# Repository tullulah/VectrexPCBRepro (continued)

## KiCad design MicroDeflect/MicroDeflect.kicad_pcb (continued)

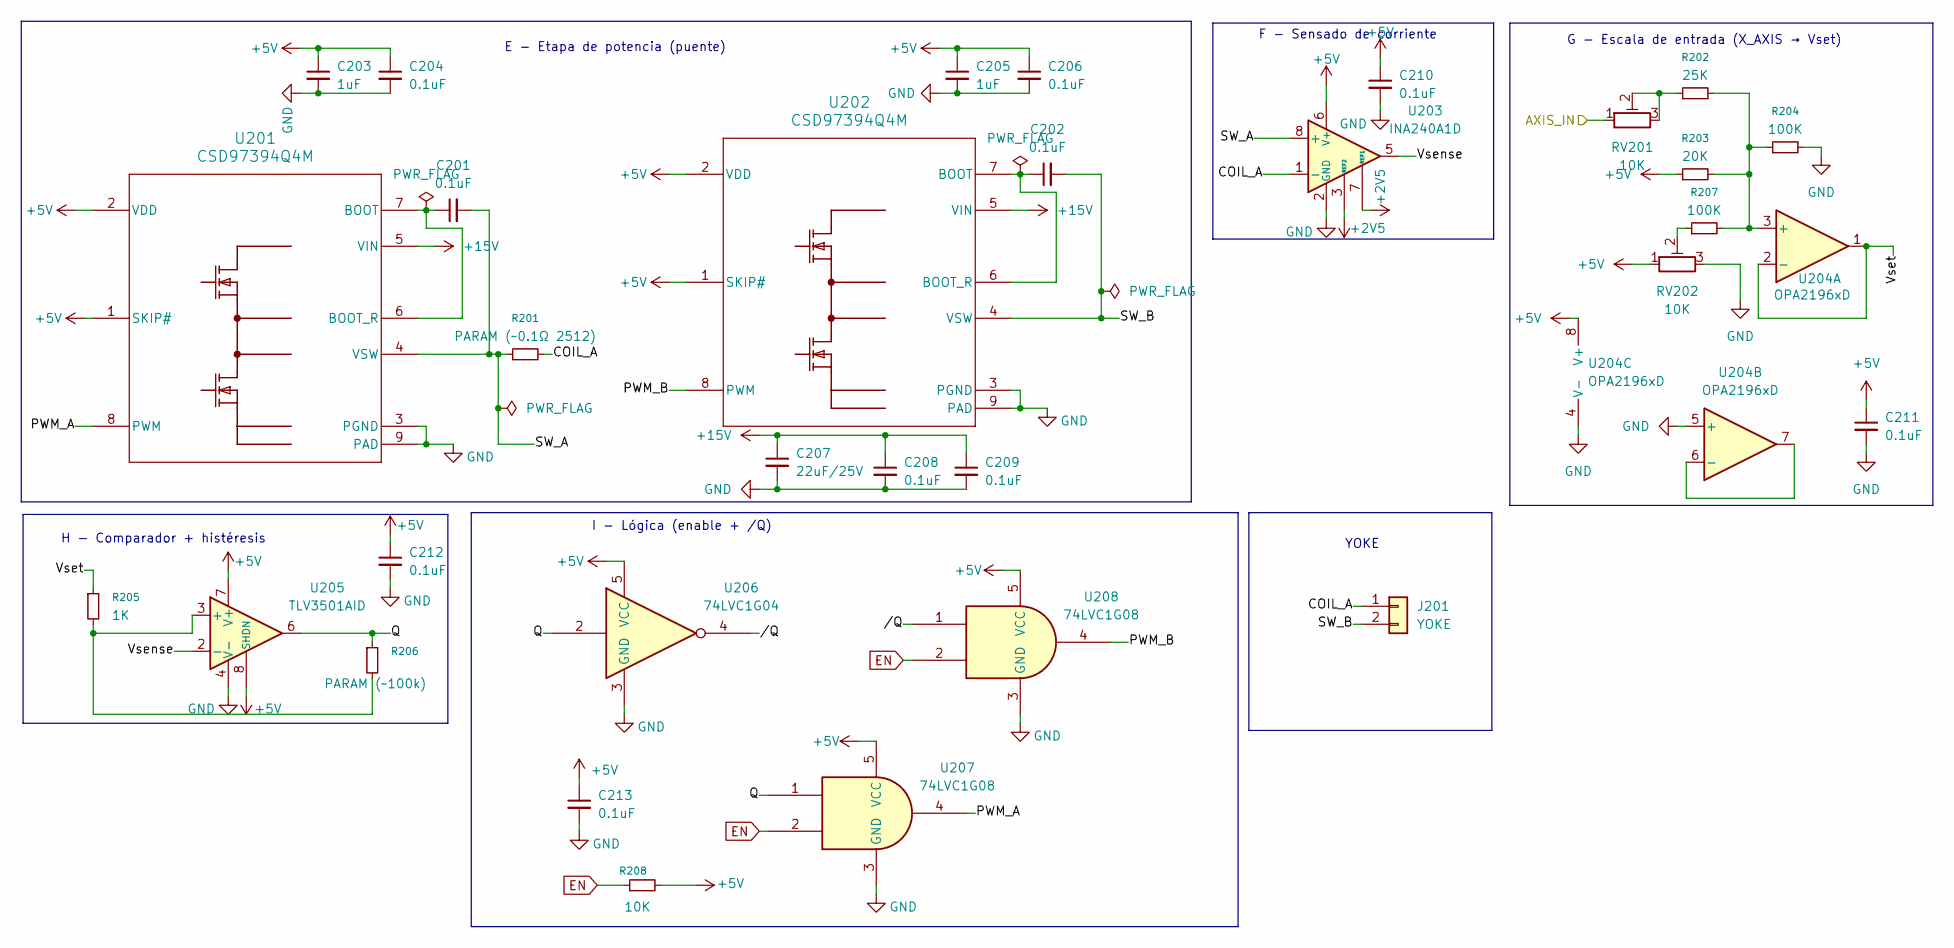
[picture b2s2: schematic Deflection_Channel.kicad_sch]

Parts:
C201, C202, C204, C206, C208, C209, C210, C211, C212, C213: 0.1uF; C_0402_1005Metric
C203, C205: 1uF; C_0402_1005Metric
C207: 22uF/25V; C_1206_3216Metric
J201: YOKE; JST_XH_B2B-XH-AM_1x02_P2.50mm_Vertical
R201: PARAM (~0.1Ω 2512); R_2512_6332Metric
R202: 25K; R_0402_1005Metric
R203: 20K; R_0402_1005Metric
R204, R207: 100K; R_0402_1005Metric
R205: 1K; R_0402_1005Metric
R206: PARAM (~100k); R_0402_1005Metric
R208: 10K; R_0402_1005Metric
RV201, RV202: 10K; Potentiometer_Bourns_3339H_Vertical
U201, U202: CSD97394Q4M; DPC0008A
U203: INA240A1D; SOIC-8_3.9x4.9mm_P1.27mm
U204: OPA2196xD; SOIC-8_3.9x4.9mm_P1.27mm
U205: TLV3501AID; SOIC-8_3.9x4.9mm_P1.27mm
U206: 74LVC1G04; SOT-23-5
U207, U208: 74LVC1G08; SOT-23-5

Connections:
+2V5: U203.3 (REF2), U203.7 (REF1); also elsewhere on the board
+5V: C203.1, C204.1, C205.1, C206.1, C210.1, C211.1, C212.1, C213.1, R203.1, R208.2, RV202.1, U201.1 (SKIP#), U201.2 (VDD), U202.1 (SKIP#), U202.2 (VDD), U203.6 (V+), U204.8 (V+), U205.7 (V+), U205.8 (SHDN), U206.5 (VCC), U207.5 (VCC), U208.5 (VCC); also elsewhere on the board
+15V: C207.1, C208.1, C209.1, U201.5 (VIN), U202.5 (VIN); also elsewhere on the board
/Deflection_Channel_X/AXIS_IN: RV201.1; also elsewhere on the board
/Deflection_Channel_X/COIL_A: J201.1, R201.2, U203.1 (-)
/Deflection_Channel_X/PWM_A: U201.8 (PWM), U207.4
/Deflection_Channel_X/PWM_B: U202.8 (PWM), U208.4
/Deflection_Channel_X/Q: R206.1, U205.6, U206.2, U207.1
/Deflection_Channel_X/SW_A: C201.2, R201.1, U201.4 (VSW), U203.8 (+)
/Deflection_Channel_X/SW_B: C202.2, J201.2, U202.4 (VSW)
/Deflection_Channel_X/Vsense: U203.5, U205.2 (-)
/Deflection_Channel_X/Vset: R205.1, U204.1, U204.2 (-)
/Deflection_Channel_X//Q: U206.4, U208.1
EN: R208.1, U207.2, U208.2; also elsewhere on the board
GND: C203.2, C204.2, C205.2, C206.2, C207.2, C208.2, C209.2, C210.2, C211.2, C212.2, C213.2, R204.2, RV202.3, U201.3 (PGND), U201.9 (PAD), U202.3 (PGND), U202.9 (PAD), U203.2 (GND), U203.4 (GND), U204.4 (V-), U204.5 (+), U205.4 (V-), U206.3 (GND), U207.3 (GND), U208.3 (GND); also elsewhere on the board
unnamed: R202.1, RV201.2, RV201.3
unnamed: R207.1, RV202.2
unnamed: C201.1, U201.6 (BOOT_R), U201.7 (BOOT)
unnamed: C202.1, U202.6 (BOOT_R), U202.7 (BOOT)
unnamed: R202.2, R203.2, R204.1, R207.2, U204.3 (+)
unnamed: U204.6 (-), U204.7
unnamed: R205.2, R206.2, U205.3 (+)

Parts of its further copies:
C301, C302, C304, C306, C308, C309, C310, C311, C312, C313: 0.1uF; C_0402_1005Metric
C303, C305: 1uF; C_0402_1005Metric
C307: 22uF/25V; C_1206_3216Metric
J301: YOKE; JST_XH_B2B-XH-AM_1x02_P2.50mm_Vertical
R301: PARAM (~0.1Ω 2512); R_2512_6332Metric
R302: 25K; R_0402_1005Metric
R303: 20K; R_0402_1005Metric
R304, R307: 100K; R_0402_1005Metric
R305: 1K; R_0402_1005Metric
R306: PARAM (~100k); R_0402_1005Metric
R308: 10K; R_0402_1005Metric
RV301, RV302: 10K; Potentiometer_Bourns_3339H_Vertical
U301, U302: CSD97394Q4M; DPC0008A
U303: INA240A1D; SOIC-8_3.9x4.9mm_P1.27mm
U304: OPA2196xD; SOIC-8_3.9x4.9mm_P1.27mm
U305: TLV3501AID; SOIC-8_3.9x4.9mm_P1.27mm
U306: 74LVC1G04; SOT-23-5
U307, U308: 74LVC1G08; SOT-23-5

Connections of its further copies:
+2V5: U303.3 (REF2), U303.7 (REF1); also elsewhere on the board
+5V: C303.1, C304.1, C305.1, C306.1, C310.1, C311.1, C312.1, C313.1, R303.1, R308.2, RV302.1, U301.1 (SKIP#), U301.2 (VDD), U302.1 (SKIP#), U302.2 (VDD), U303.6 (V+), U304.8 (V+), U305.7 (V+), U305.8 (SHDN), U306.5 (VCC), U307.5 (VCC), U308.5 (VCC); also elsewhere on the board
+15V: C307.1, C308.1, C309.1, U301.5 (VIN), U302.5 (VIN); also elsewhere on the board
/Deflection_Channel_Y/AXIS_IN: RV301.1; also elsewhere on the board
/Deflection_Channel_Y/COIL_A: J301.1, R301.2, U303.1 (-)
/Deflection_Channel_Y/PWM_A: U301.8 (PWM), U307.4
/Deflection_Channel_Y/PWM_B: U302.8 (PWM), U308.4
/Deflection_Channel_Y/Q: R306.1, U305.6, U306.2, U307.1
/Deflection_Channel_Y/SW_A: C301.2, R301.1, U301.4 (VSW), U303.8 (+)
/Deflection_Channel_Y/SW_B: C302.2, J301.2, U302.4 (VSW)
/Deflection_Channel_Y/Vsense: U303.5, U305.2 (-)
/Deflection_Channel_Y/Vset: R305.1, U304.1, U304.2 (-)
/Deflection_Channel_Y//Q: U306.4, U308.1
EN: R308.1, U307.2, U308.2; also elsewhere on the board
GND: C303.2, C304.2, C305.2, C306.2, C307.2, C308.2, C309.2, C310.2, C311.2, C312.2, C313.2, R304.2, RV302.3, U301.3 (PGND), U301.9 (PAD), U302.3 (PGND), U302.9 (PAD), U303.2 (GND), U303.4 (GND), U304.4 (V-), U304.5 (+), U305.4 (V-), U306.3 (GND), U307.3 (GND), U308.3 (GND); also elsewhere on the board
unnamed: R302.1, RV301.2, RV301.3
unnamed: R307.1, RV302.2
unnamed: C301.1, U301.6 (BOOT_R), U301.7 (BOOT)
unnamed: C302.1, U302.6 (BOOT_R), U302.7 (BOOT)
unnamed: R302.2, R303.2, R304.1, R307.2, U304.3 (+)
unnamed: U304.6 (-), U304.7
unnamed: R305.2, R306.2, U305.3 (+)

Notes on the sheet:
YOKE
I - Lógica (enable + /Q)
H - Comparador + histéresis
G - Escala de entrada (X_AXIS → Vset)
F - Sensado de corriente
E - Etapa de potencia (puente)

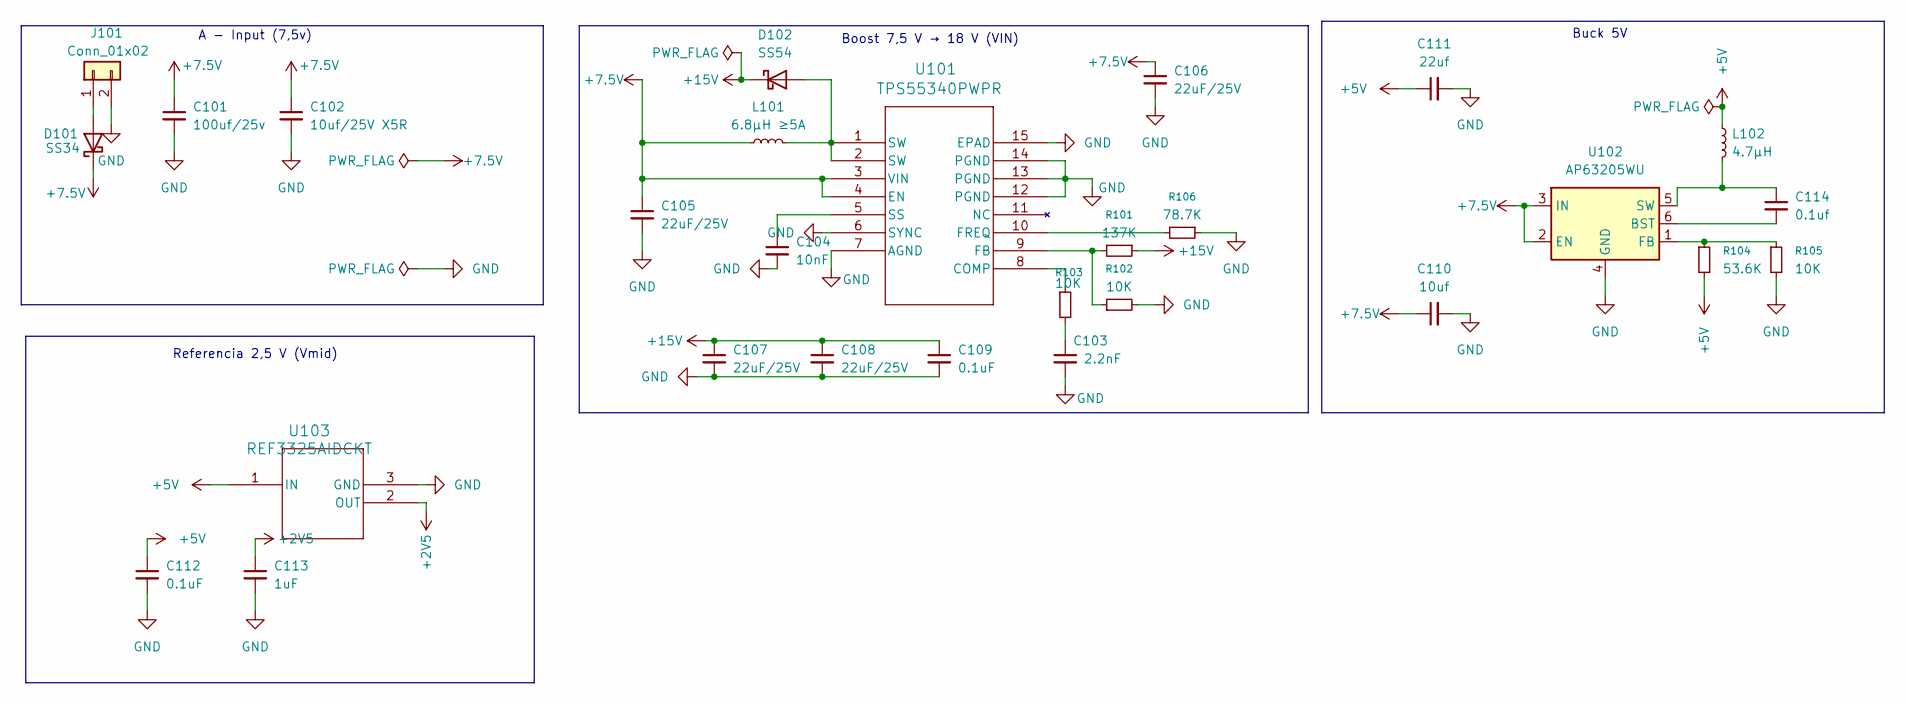
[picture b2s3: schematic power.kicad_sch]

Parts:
C101: 100uf/25v; CP_Elec_6.3x7.7
C102: 10uf/25V X5R; C_0805_2012Metric
C103: 2.2nF; C_0402_1005Metric
C104: 10nF; C_0402_1005Metric
C105, C106, C107, C108: 22uF/25V; C_1206_3216Metric
C109, C112: 0.1uF; C_0402_1005Metric
C110: 10uf; C_0805_2012Metric
C111: 22uf; C_0805_2012Metric
C113: 1uF; C_0402_1005Metric
C114: 0.1uf; C_0402_1005Metric
D101: SS34; D_SMA
D102: SS54; D_SMB
J101: Conn_01x02; JST_VH_B2P-VH-B_1x02_P3.96mm_Vertical
L101: 6.8µH ≥5A; L_12x12mm_H6mm
L102: 4.7µH; L_Bourns_SRN6045TA
R101: 137K; R_0402_1005Metric
R102, R103, R105: 10K; R_0402_1005Metric
R104: 53.6K; R_0402_1005Metric
R106: 78.7K; R_0402_1005Metric
U101: TPS55340PWPR; PWP14
U102: AP63205WU; TSOT-23-6
U103: REF3325AIDCKT; DCK3

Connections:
+2V5: C113.1, U103.2 (OUT); also elsewhere on the board
+5V: C111.1, C112.1, L102.1, R104.2, U103.1 (IN); also elsewhere on the board
+7.5V: C101.1, C102.1, C105.1, C106.1, C110.1, D101.1 (K), L101.1, U101.3 (VIN), U101.4 (EN), U102.2 (EN), U102.3 (IN)
+15V: C107.1, C108.1, C109.1, D102.1 (K), R101.1; also elsewhere on the board
GND: C101.2, C102.2, C103.2, C104.2, C105.2, C106.2, C107.2, C108.2, C109.2, C110.2, C111.2, C112.2, C113.2, J101.2, R102.2, R105.2, R106.1, U101.6 (SYNC), U101.7 (AGND), U101.12 (PGND), U101.13 (PGND), U101.14 (PGND), U101.15 (EPAD), U102.4 (GND), U103.3 (GND); also elsewhere on the board
unnamed: C103.1, R103.2
unnamed: D101.2 (A), J101.1
unnamed: D102.2 (A), L101.2, U101.1 (SW), U101.2 (SW)
unnamed: R103.1, U101.8 (COMP)
unnamed: R101.2, R102.1, U101.9 (FB)
unnamed: R106.2, U101.10 (FREQ)
unnamed: C104.1, U101.5 (SS)
unnamed: C114.2, U102.6 (BST)
unnamed: R104.1, R105.1, U102.1 (FB)
unnamed: C114.1, L102.2, U102.5 (SW)

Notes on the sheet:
Boost 7,5 V → 18 V (VIN)
Referencia 2,5 V (Vmid)
Buck 5V
A - Input (7,5v)

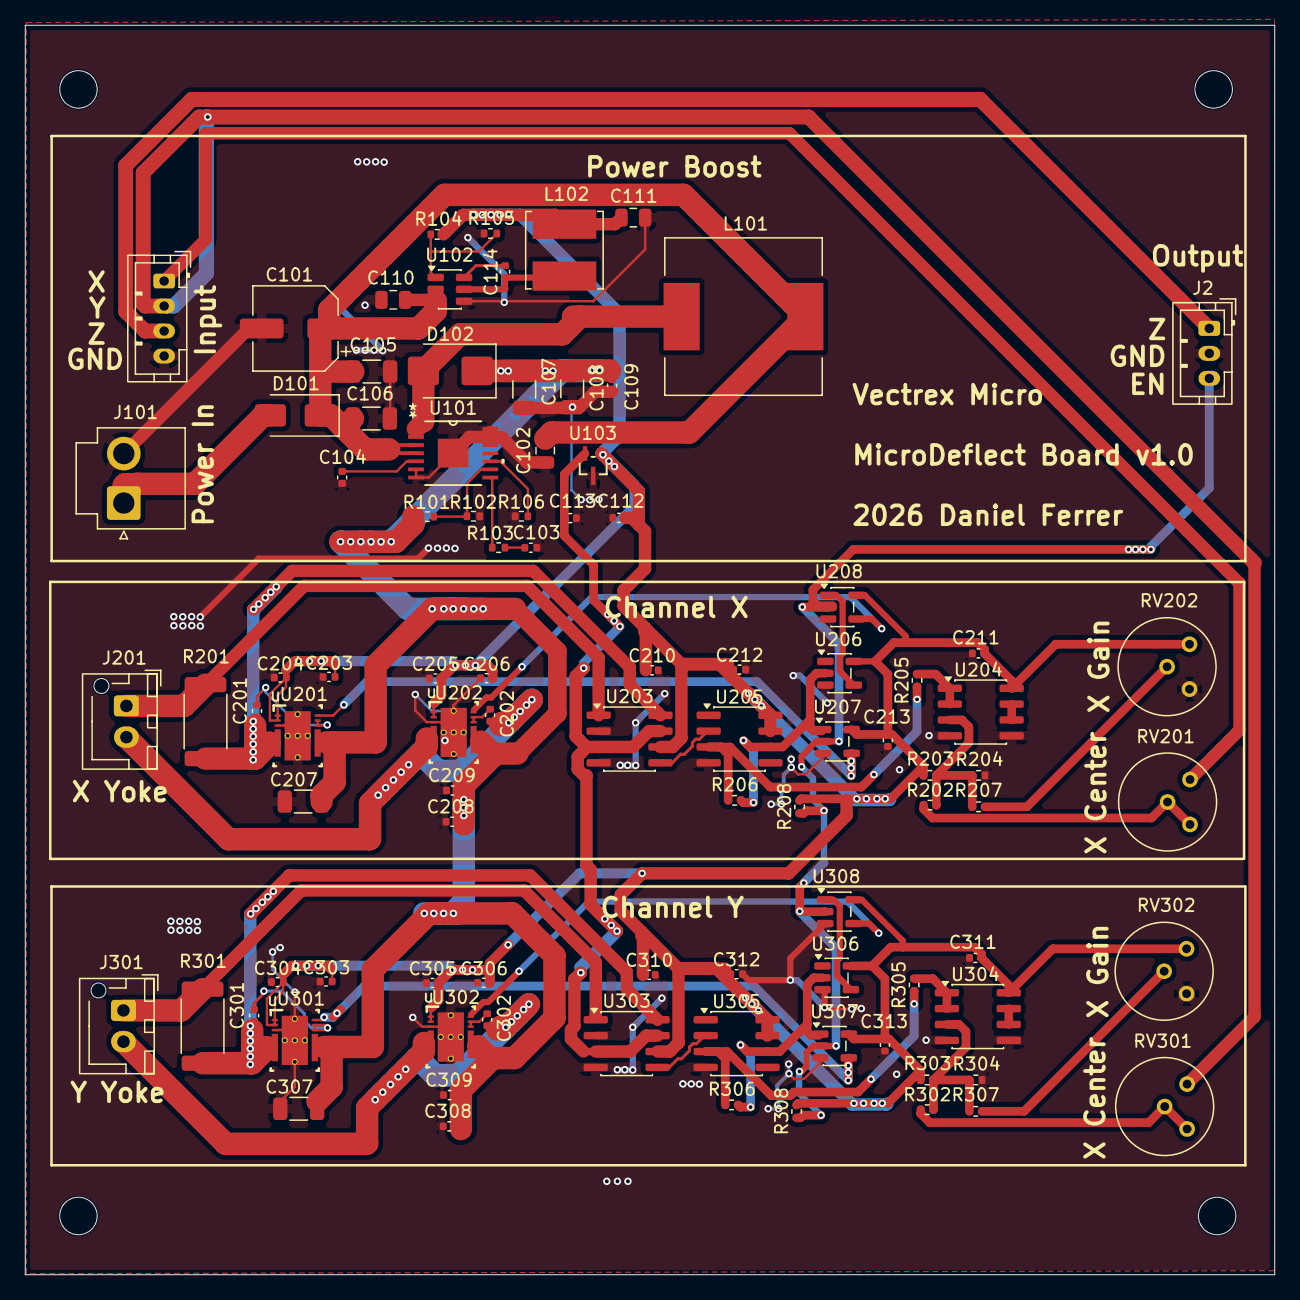
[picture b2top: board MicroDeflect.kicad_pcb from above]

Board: 2 copper layers, 100.0 x 100.0 mm, 98 parts (0 on the bottom side), 51 nets.

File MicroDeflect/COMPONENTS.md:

# Deflection Board — Components by group

Reference-designator scheme: **Power = 1xx · Channel X = 2xx · Channel Y = 3xx**.
`BOM_preliminary.csv` is the flat single-source-of-truth; this file is the readable
grouped view and shows **which sheet each group lives on**.

---

## Sheet: POWER (1xx)

### A — Input 7.5 V
| Ref | Value | Function |
|---|---|---|
| J101 | 7.5V_IN | power input connector |
| D101 | SS34 | reverse-polarity protection |
| C101 | 100µF/25V | input bulk |
| C102 | 10µF/25V | input decoupling |

### B — Boost 7.5 V → 18 V (VIN)
| Ref | Value | Function |
|---|---|---|
| U101 | TPS55340 | boost IC |
| L101 | 6.8µH ≥5A | boost inductor |
| D102 | SS54 | boost rectifier |
| R101 | 137k | FB top (→18V) |
| R102 | 10k | FB bottom |
| R103 | 10k | COMP R (per datasheet) |
| C103 | 2.2nF | COMP C (per datasheet) |
| C104 | 10nF | soft-start (per datasheet) |
| C105, C106 | 22µF/25V | boost input |
| C107, C108 | 22µF/25V | boost output |
| C109 | 0.1µF | boost output HF |

### C — Buck 5 V
| Ref | Value | Function |
|---|---|---|
| U102 | AP63205 | buck IC (from +7V5) |
| L102 | 4.7µH | buck inductor |
| R104 | 53.6k | FB top (→5V) |
| R105 | 10k | FB bottom |
| C110 | 10µF | buck input |
| C111 | 22µF | buck output |

### D — 2.5 V reference (Vmid)
| Ref | Value | Function |
|---|---|---|
| U103 | REF3325 | 2.5V reference |
| C112 | 0.1µF | decoupling |
| C113 | 1µF | decoupling |

---

## Sheet: DEFLECTION_CHANNEL — X = 2xx · Y = 3xx (same parts)

### E — Power stage (H-bridge)
| Ref | Value | Function |
|---|---|---|
| U201 | CSD97394Q4M | leg A |
| U202 | CSD97394Q4M | leg B |
| R201 | **PARAMETRIC** (~0.1Ω 2512) | R_sense (shunt) |
| C201, C202 | 0.1µF | BOOT leg A / B |
| C203, C205 | 1µF | VDD leg A / B |
| C204, C206 | 0.1µF | VDD HF leg A / B |
| C207 | 22µF/25V | VIN local bulk |
| C208, C209 | 0.1µF | VIN local A / B |

### F — Current sense
| Ref | Value | Function |
|---|---|---|
| U203 | INA240A1 | current sense (REF=Vmid) |
| C210 | 0.1µF | decoupling |

### G — Input scale (X_AXIS → Vset)
| Ref | Value | Function |
|---|---|---|
| U204 | OPA2196 | buffer (unit A; unit B spare) |
| C211 | 0.1µF | decoupling |
| R202 | 25k | Rin1 (from X_AXIS) |
| R203 | 20k | Rin2 (from +5V, offset) |
| R204 | 100k | Rf (to GND) |
| RV201 | 10k | gain trim (optional) |
| RV202 | 10k | offset/centering trim (optional) |

### H — Comparator + hysteresis
| Ref | Value | Function |
|---|---|---|
| U205 | TLV3501 | comparator |
| C212 | 0.1µF | decoupling |
| R205 | 1k | Rin (Vset → comparator +) |
| R206 | **PARAMETRIC** (~100k) | Rhys (hysteresis) |

### I — Logic (enable + /Q)
| Ref | Value | Function |
|---|---|---|
| U206 | 74LVC1G04 | inverter (/Q) |
| U207 | 74LVC1G08 | AND: PWM_A = Q & EN |
| U208 | 74LVC1G08 | AND: PWM_B = /Q & EN |
| C213 | 0.1µF | decoupling |

### J — Yoke
| Ref | Value | Function |
|---|---|---|
| J201 | Conn_01x02 | yoke X coil |

---

## Power symbols & signals (no reference designator)
- **Power symbols** (auto-connect by name across all sheets):
  `+7V5`, `+18V` (=VIN), `+5V`, `+2V5` (=VMID), `GND`, plus `PWR_FLAG` on each generated rail.
- **Signal:** `EN` (global label) — from the spot killer; tie to `+5V` for bench bring-up.

## Not on these sheets yet
- **Interface / spot-killer activity detector** → its own sheet (4xx), TBD.
- **Z_AXIS** passes straight through to the HV board (not used here).

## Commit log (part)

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2020-09-27 add PCB scan images (600dpi)
2024-08-19 First PCB Version
2024-08-19 added lm386 audio circuit
2024-08-19 remove unused files
2024-08-20 Adjusted rules to JLCPCB Capacities. Solved all DRC Erros and conflicts
2024-08-20 added lm386 again, Added MD_90SM footprint. Solve all DRC Conflicts
2024-08-20 updated powerlines to 5mm, solve DRC conflicts
2024-08-20 resolve DRC violations, various shorts to +5V
2024-08-20 fixed missing traces. fixed reset button connector. fixed some DRC warnings
2024-08-20 clean up a few areas, including the XTAL
2024-08-20 update cart connector to AMP 5645384-1 with 3D model
2024-08-21 Remove all tracks, change RAM, change ROM, change electrolitic caps
2024-09-02 iteration 2
2024-09-02 add iteration 2 images
2024-09-03 changed packages and symbols to fit Mouser BOM
2024-09-09 Iteration 3
2026-06-15 Checkpoint before project rename to MicroDeflect
